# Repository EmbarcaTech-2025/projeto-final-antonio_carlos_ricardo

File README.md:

# Projeto final - EmbarcaTech 2025

Autores: **Carlos Martinez Perez** e **Ricardo Jorge Furlan**

Curso: Residência Tecnológica em Sistemas Embarcados

Instituição: EmbarcaTech - HBr

Campinas 08, setembro de 2025.

---

## ⚠ Disclaimer
## THE SOFTWARE IS PROVIDED "AS IS", USE AT YOUR OWN RISK
## O SOFTWARE É FORNECIDO "COMO ESTÁ", USE POR SUA CONTA E RISCO

## This code was developed for educational purposes as an assignment for Phase 2 of the residency program in the **EmbarcaTech professional training program**, with the goal of demonstrating some of the concepts learned during the residency.

## Third-Party Code

- The files for controlling the **OLED display** (`ssd1306_...` files), including the text fonts, were based on the repository:  
  https://github.com/BitDogLab/BitDogLab-C/tree/main/display_oled_logo/inc with minor modifications.
- The `pico_sdk_import.cmake` file was **automatically generated** during project creation by the **Raspberry Pi Pico plugin**.
- The `CMakeLists.txt` file was initially **automatically generated** during project creation by the **Raspberry Pi Pico plugin**, and later edited as needed for the project.

## How to Build/Compile the Code

This software was developed for the **BitDogLab V6.3** board. This board uses the **Raspberry Pi Pico_W** board (which contains the **RP2040 microcontroller**).

For development, the **Visual Studio Code IDE** was used along with the **Raspberry Pi Pico plugin**. The SDK version used was **2.2.0**.

---

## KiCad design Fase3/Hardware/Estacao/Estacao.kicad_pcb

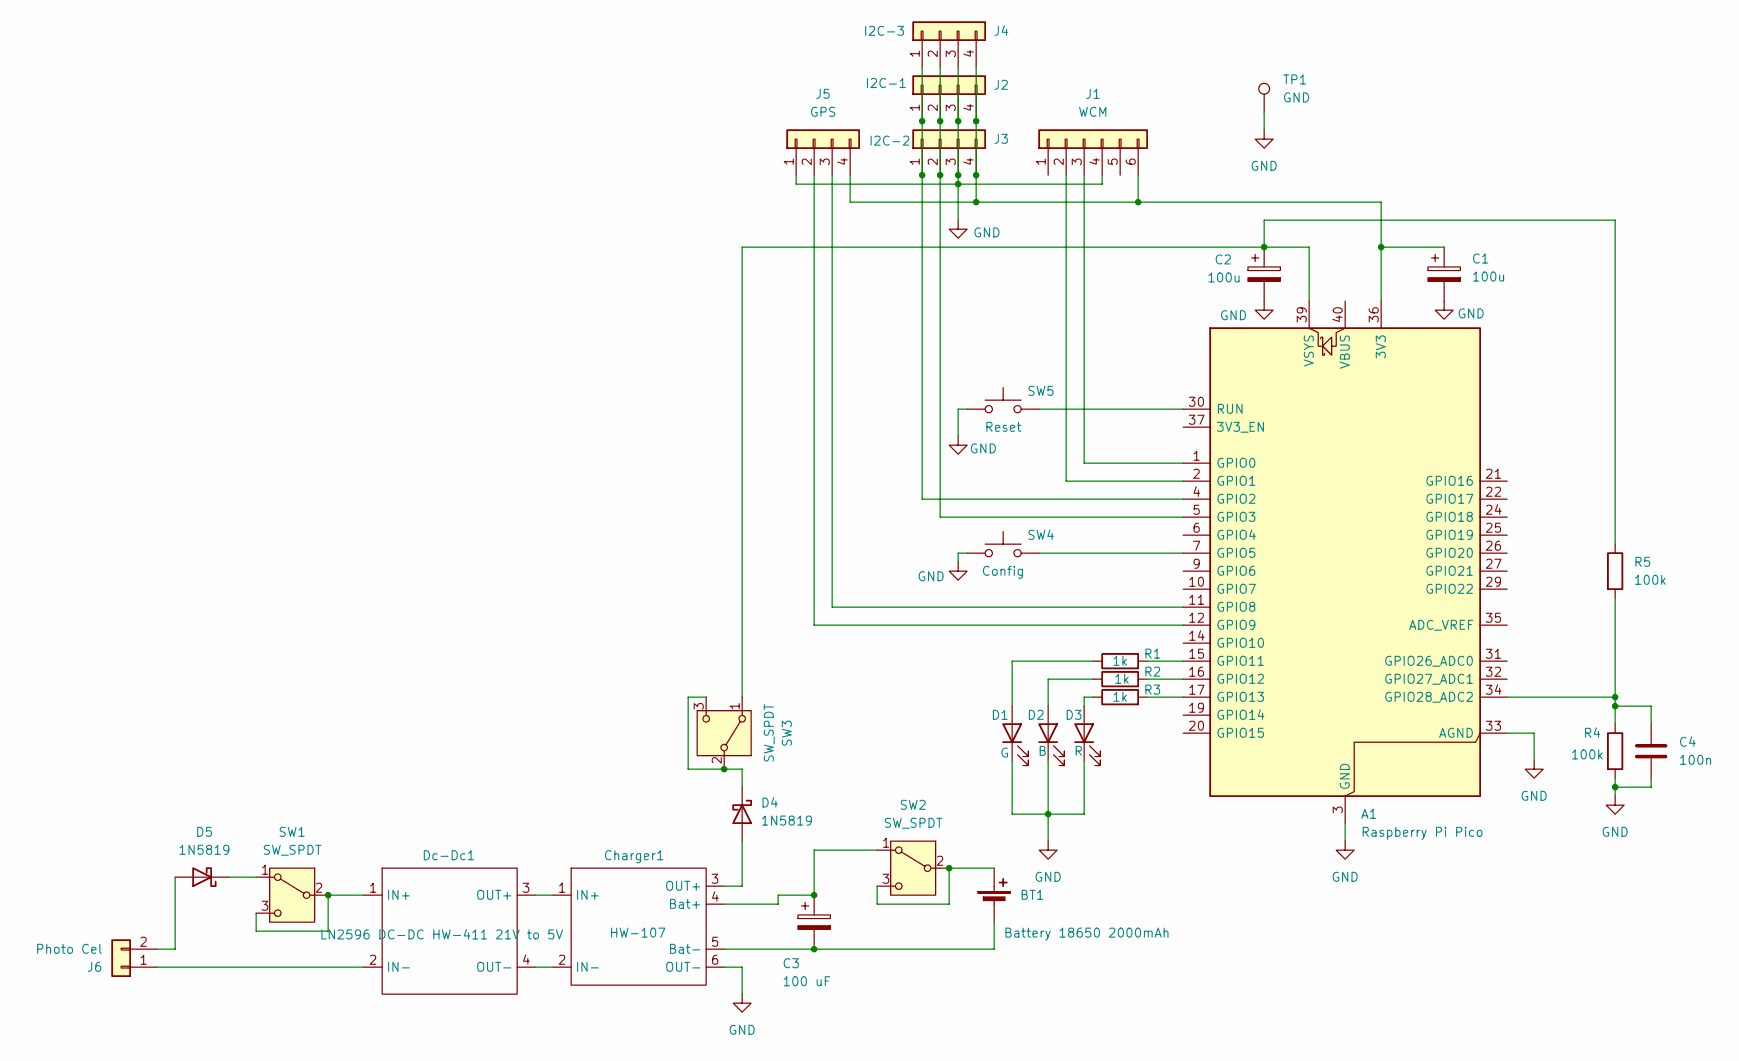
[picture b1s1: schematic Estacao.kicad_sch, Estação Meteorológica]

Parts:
A1: Raspberry Pi Pico; RaspberryPi_Pico_Common_Unspecified
BT1: Battery 18650 2000mAh; BatteryHolder_MPD_BK-18650-PC2b
C1, C2: 100u; CP_Radial_D8.0mm_P3.50mm
C3: 100 uF; CP_Radial_D8.0mm_P3.50mm
C4: 100n; C_Disc_D5.0mm_W2.5mm_P5.00mm
Charger1: HW-107; Charger
D1: G; LED_D5.0mm
D2: B; LED_D5.0mm
D3: R; LED_D5.0mm
D4, D5: 1N5819; D_DO-41_SOD81_P10.16mm_Horizontal
Dc-Dc1: LN2596 DC-DC HW-411 21V to 5V; Dc_DC
J1: WCM; PinSocket_1x06_P2.54mm_Vertical
J2: I2C-1; JST_XH_B4B-XH-A_1x04_P2.50mm_Vertical
J3: I2C-2; JST_XH_B4B-XH-A_1x04_P2.50mm_Vertical
J4: I2C-3; JST_XH_B4B-XH-A_1x04_P2.50mm_Vertical
J5: GPS; JST_XH_B4B-XH-A_1x04_P2.50mm_Vertical
J6: Photo Cel; Molex_SL_171971-0002_1x02_P2.54mm_Vertical_b
R1, R2, R3: 1k; R_Axial_DIN0207_L6.3mm_D2.5mm_P10.16mm_Horizontal
R4, R5: 100k; R_Axial_DIN0207_L6.3mm_D2.5mm_P10.16mm_Horizontal
SW1, SW2, SW3: SW_SPDT; switch_3p_2mm_e_2.54mm
SW4: Config; SW_PUSH_6mm
SW5: Reset; SW_PUSH_6mm
TP1: GND; PinHeader_1x01_P2.54mm_Vertical

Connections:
GND: A1.3 (GND), A1.8 (GND), A1.13 (GND), A1.18 (GND), A1.23 (GND), A1.28 (GND), A1.33 (AGND), A1.38 (GND), C1.2, C2.2, C4.2, Charger1.6 (OUT-), D1.1 (K), D2.1 (K), D3.1 (K), J1.4, J2.3, J3.3, J4.3, J5.1, R4.2, SW4.1, SW5.1, TP1.1
unnamed: A1.36 (3V3), C1.1, J1.6, J2.4, J3.4, J4.4, J5.4
unnamed: A1.1 (GPIO0), J1.3
unnamed: A1.2 (GPIO1), J1.2
unnamed: A1.4 (GPIO2), J2.1, J3.1, J4.1
unnamed: A1.5 (GPIO3), J2.2, J3.2, J4.2
unnamed: A1.7 (GPIO5), SW4.2
unnamed: A1.11 (GPIO8), J5.3
unnamed: A1.12 (GPIO9), J5.2
unnamed: A1.15 (GPIO11), R1.2
unnamed: A1.16 (GPIO12), R2.2
unnamed: A1.17 (GPIO13), R3.2
unnamed: A1.34 (GPIO28_ADC2), C4.1, R4.1, R5.2
unnamed: A1.30 (RUN), SW5.2
unnamed: A1.39 (VSYS), C2.1, R5.1, SW3.1 (A)
unnamed: BT1.1 (+), SW2.2 (B), SW2.3 (C)
unnamed: BT1.2 (-), C3.2, Charger1.5 (Bat-)
unnamed: C3.1, Charger1.4 (Bat+), SW2.1 (A)
unnamed: Charger1.1 (IN+), Dc-Dc1.3 (OUT+)
unnamed: Charger1.2 (IN-), Dc-Dc1.4 (OUT-)
unnamed: Charger1.3 (OUT+), D4.2 (A)
unnamed: D1.2 (A), R1.1
unnamed: D2.2 (A), R2.1
unnamed: D3.2 (A), R3.1
unnamed: D4.1 (K), SW3.2 (B), SW3.3 (C)
unnamed: D5.2 (A), J6.2
unnamed: D5.1 (K), SW1.1 (A)
unnamed: Dc-Dc1.1 (IN+), SW1.2 (B), SW1.3 (C)
unnamed: Dc-Dc1.2 (IN-), J6.1

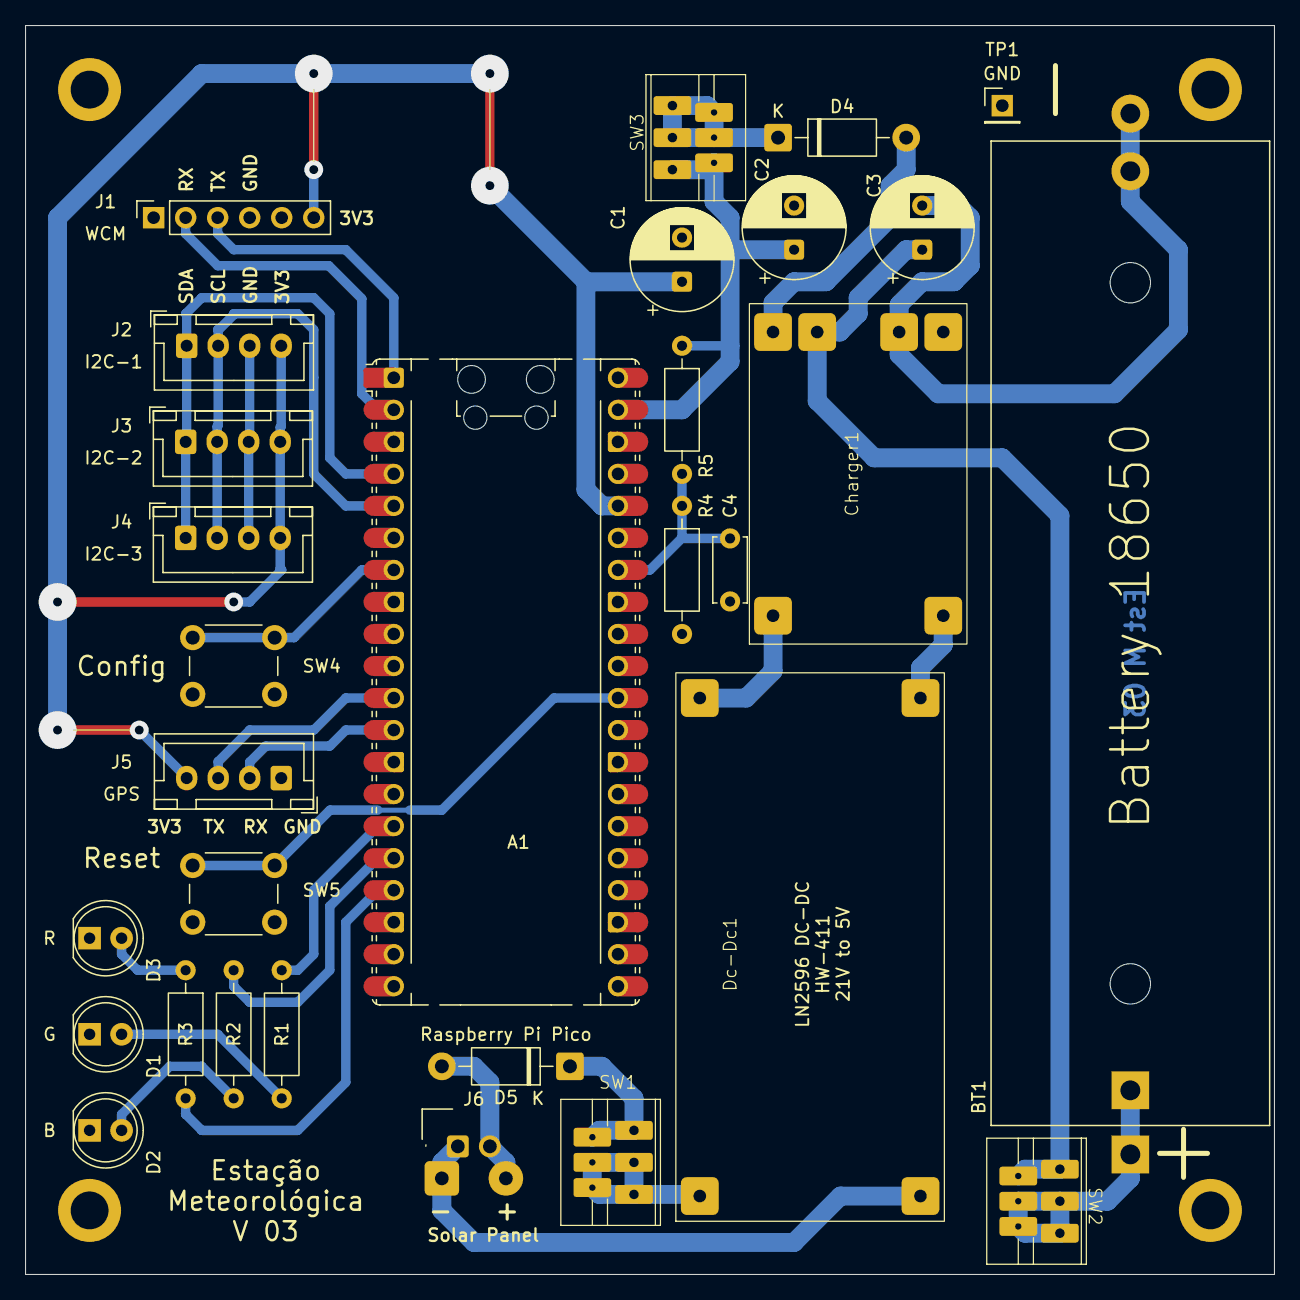
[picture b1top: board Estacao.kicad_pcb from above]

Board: 2 copper layers, 99.1 x 99.1 mm, 30 parts (0 on the bottom side), 29 nets.

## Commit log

2025-07-16 Etapa1
2025-07-18 Adicionando README
2025-07-18 Atualizando README
2025-08-08 Revisao Etapa1
2025-08-08 Revisão 1.1
2025-08-08 Rev .: 1.1 text
2025-08-08 Etapa1 Revisao 1
2025-08-08 Etapa2
2025-08-12 Add Enderecos I2C
2025-08-25 Adding EstMeteo ET3.md with prototype information
2025-08-25 Adding dashboard code in json
2025-08-25 Atualisado Codes
2025-08-25 Rename
2025-08-25 Correção de texto
2025-08-26 Updating EstMeteo Et3.md
2025-08-31 Add src build 0005
2025-09-04 Inicio Etapa 4
2025-09-15 LiftOutch
2025-09-15 Servidor
2025-09-17 Add code B0015
2025-09-18 Versão final Etapa4
2025-09-19 Add Link Videos
2025-10-12 Adding etapa1_semana1
2025-10-12 AddNovoDiagrama
2025-10-12 Adding tab_requisitos.md
2025-10-12 Update tab req
2025-10-12 Só um contexto
2025-10-14 Starting fase 3 etapa 1 semana 2
2025-10-19 Add Docs Semana2
2025-10-26 Etapa1-Semana3
2025-11-02 Add apresentacao etapa1
2025-11-08 Add Fase3 Etapa2Semana1 Parte00
2025-11-08 Add na Etapa2 Readme
2025-11-08 Updating Fase 3 - Etapa 2
2025-11-08 Adding rel_tec.md
2025-11-08 Updatin rel_tec.md
2025-11-11 Updating rel_tec.md
2025-11-15 Update images
2025-11-15 Up Et2 Sem2
2025-11-15 Renema et2sen1
2025-11-23 Atualizacao Etapa2 Semana3
2025-11-23 Add Apresentacao
2025-11-23 add ap
2025-11-30 Add RelatorioEstapa3Semana1
2025-12-06 Add Code estacao
2025-12-06 Add Pic Current
2025-12-07 Add Relatorio Preliminar Et3Sem2
2025-12-08 Code-Build 0003
2025-12-13 Add Etapa3Semana3
2026-01-04 Atualização sources
2026-01-04 Add Relatorio Etapa3 Semana4
2026-01-04 Add Apresentaçao
2026-01-04 Atualizaçao apresentação
2026-01-11 Add Relatorio Etapa4 Semana1
2026-01-11 Updade SRC estação
2026-01-17 Add PayloadDecode 0003
2026-01-17 Estacao Build: 0016
2026-01-18 Update Et4Semana2-01
2026-01-18 Update02
2026-01-21 Add PCB
2026-01-22 Updade Slik da PCB V01
2026-01-23 Add relatorio
2026-01-25 ManualTmp
2026-01-25 rev manual
2026-01-26 pcb v02-00
2026-01-28 Build 0021
2026-01-31 Add Rel et4sem4
2026-01-31 Update Est Src Build 0023
2026-01-31 Update PCB V03
2026-01-31 Add relatório TRL
2026-02-01 Manual e Slides
2026-02-01 Atualizacao Manual
2026-02-01 Correção XIAO
2026-02-01 Build 0024
2026-02-04 UpdatePcb V3
2026-02-07 Etapa5
2026-02-07 UpdateCode build: 0028
2026-02-08 Code Build0033
2026-02-15 Repositorio
2026-02-15 Relatorio
2026-02-15 CodeStationBuild0039
2026-02-18 Update TTN Decoder 0006
2026-02-18 Code Build:0040
2026-02-19 Code Build:0041
2026-02-22 Atualizacao final
2026-02-25 Update WCM correcao SF, build0006
2026-02-25 WCM: Versão 0.00.07 - 25/02/2026 - Build: 0007 - Remoção das mensagens de debug
2026-03-03 Add no dir KiCad main board fp-lib-table
2026-04-07 Update MainBoard to build0042
2026-04-07 WCM-Code add AUTO 0-7, 8-15 e 0-15
